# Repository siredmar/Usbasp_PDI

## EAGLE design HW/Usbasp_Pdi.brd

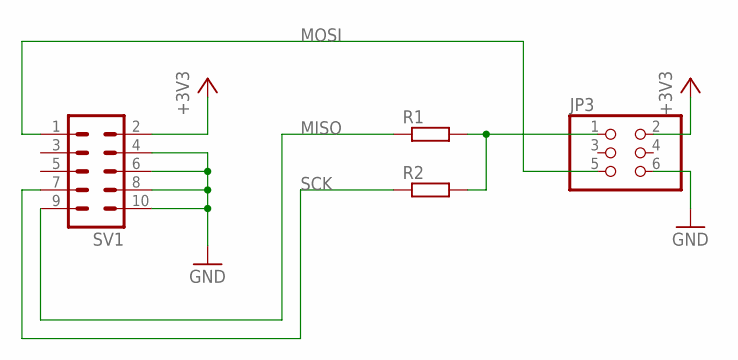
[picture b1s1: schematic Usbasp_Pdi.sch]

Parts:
JP3: PINHD-2X03_2.54; 2X03
R1, R2: R-EU_R0603; R0603
SV1: ML10

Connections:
+3V3: JP3.2, SV1.2
GND: JP3.6, SV1.4, SV1.6, SV1.8, SV1.10
MISO: R1.1, SV1.9
MOSI: JP3.5, SV1.1
unnamed: JP3.1, R1.2, R2.2
SCK: R2.1, SV1.7

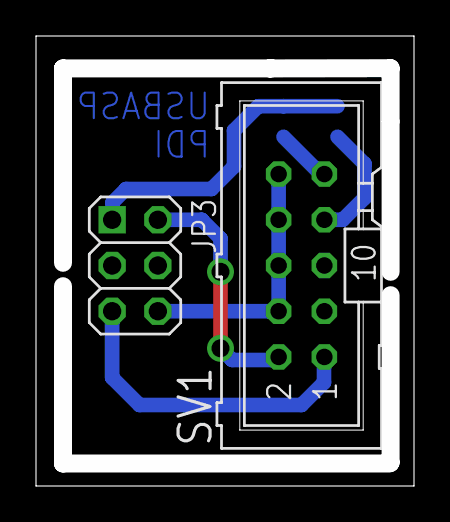
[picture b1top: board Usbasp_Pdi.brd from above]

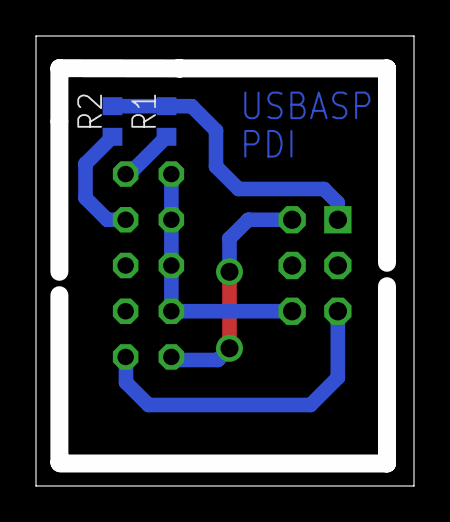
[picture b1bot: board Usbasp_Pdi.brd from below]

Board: 2 copper layers, 20.0 x 24.0 mm, 4 parts (2 on the bottom side), 6 nets.

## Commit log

2016-06-16 Added patched versions of avrdude, usbasp firmware. Added adapter board for 3.3V Usbasp devices
2016-06-16 Added picture of programmer
